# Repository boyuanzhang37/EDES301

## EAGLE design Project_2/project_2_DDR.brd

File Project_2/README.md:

Project 2
Contains the schematic, board, and the library of the DDR game board, folders contain further manufacturing information

The project: 

The entire design is a revision of project 1 rearranged into a more compact format on a PCB
  Contains 7 Segment display, 2 buzzers, 8 leds with 4 red and 4 blue, and a joystick
All components are placed on the top mianly because the input and the output of the game should be on the same side (dispaly, leds, joystick) and there were space for the buzzers and the pocketbeagel to fit without issues.

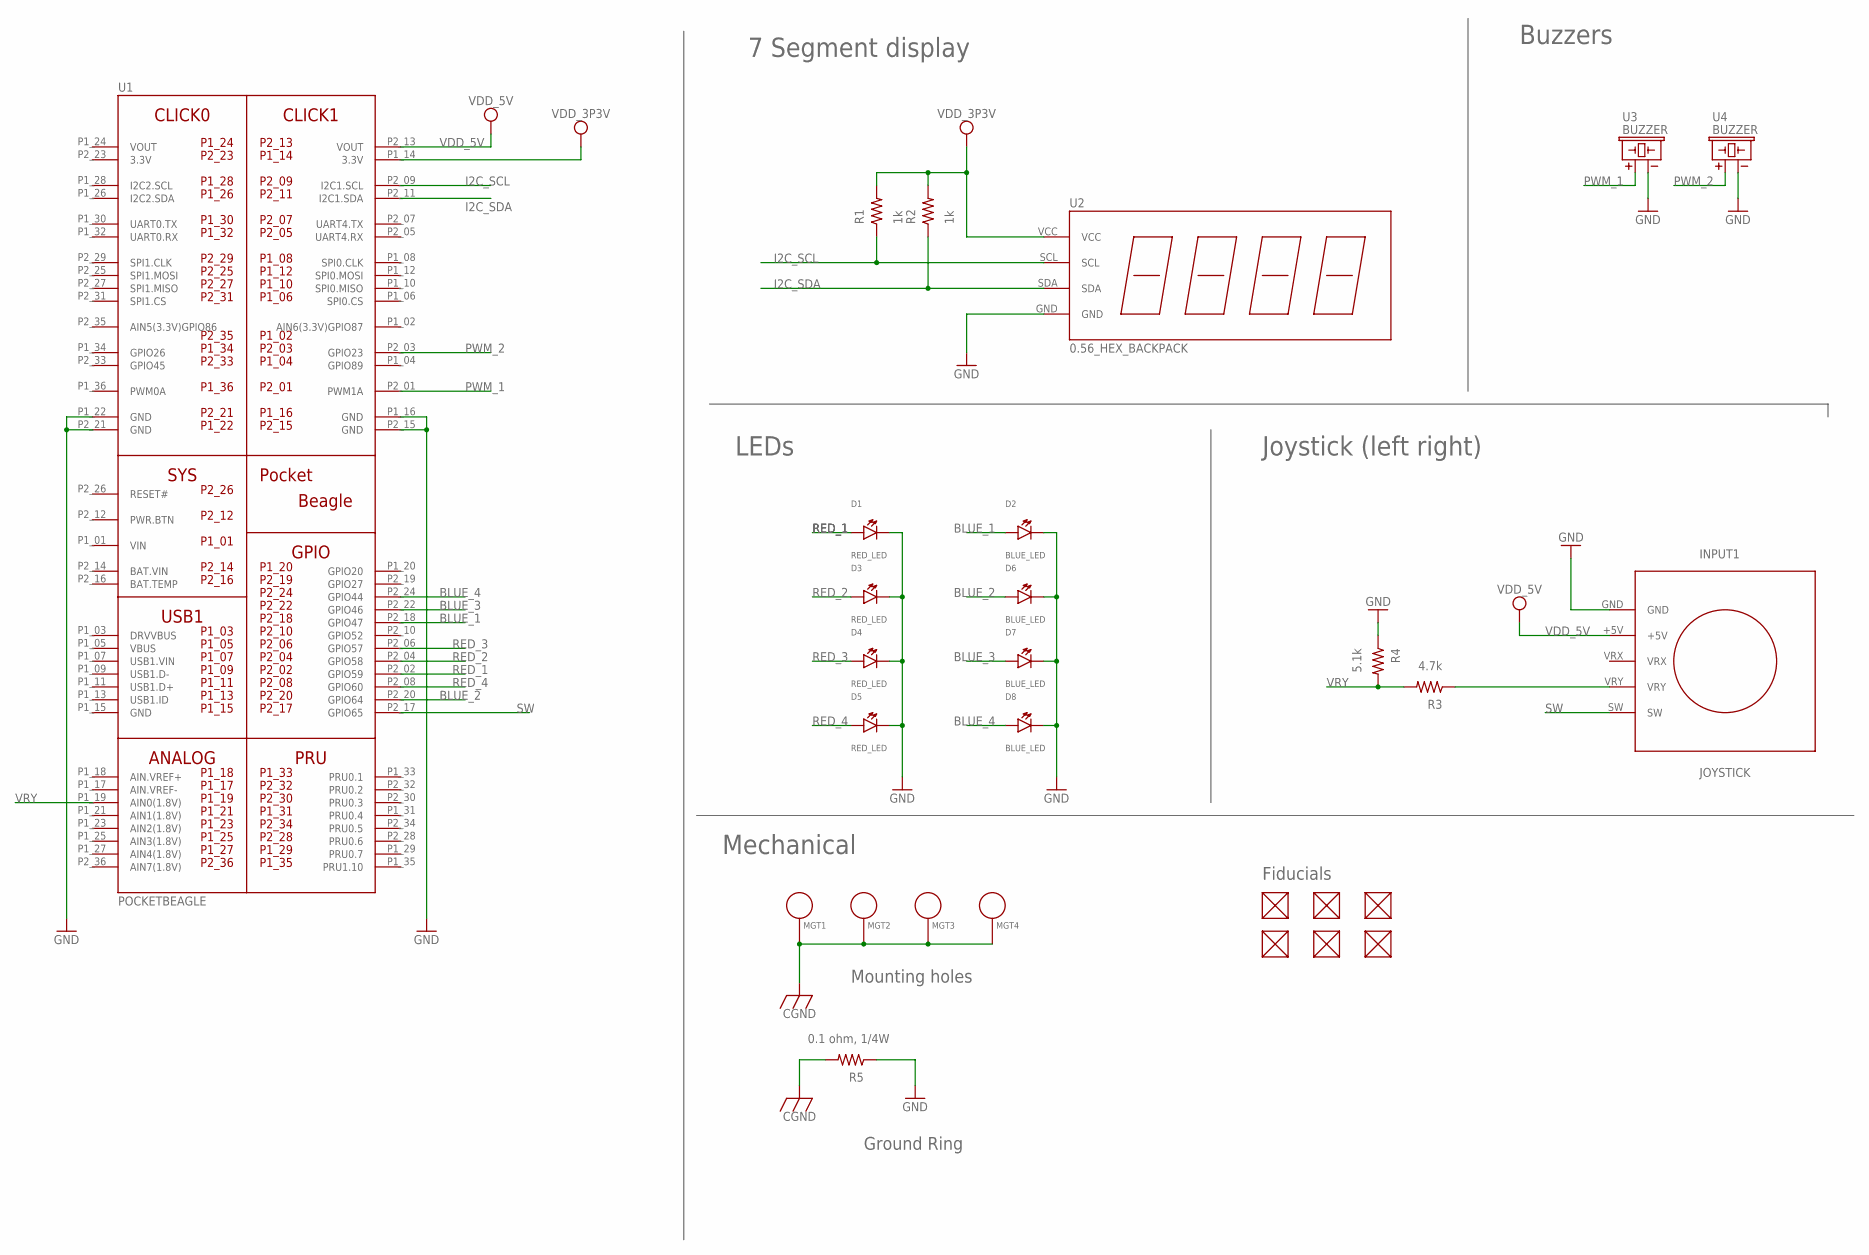
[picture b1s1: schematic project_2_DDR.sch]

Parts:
D1, D3, D4, D5: RED_LED; EIA-STD
D2, D6, D7, D8: BLUE_LED; EIA-STD
FUD1, FUD2, FUD3, FUD4, FUD5, FUD6: FIDUCIAL; FIDUCIAL_40MIL
INPUT1: JOYSTICK
MGT1, MGT2, MGT3, MGT4: MOUNTING_HOLE
R1, R2: 1k; R0603
R3: 4.7k; R0603
R4: 5.1k; R0603
R5: 0.1 ohm, 1/4W; R0603
U1: POCKETBEAGLE
U2: 0.56_HEX_BACKPACK
U3, U4: BUZZER; BUZZER_6.5MM

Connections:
3.3V: U1.P2_23 (3.3V)
BAT.VIN: U1.P2_14 (BAT.VIN)
BLUE_1: D2.ANODE, U1.P2_18 (GPIO47)
BLUE_2: D6.ANODE, U1.P2_20 (GPIO64)
BLUE_3: D7.ANODE, U1.P2_22 (GPIO46)
BLUE_4: D8.ANODE, U1.P2_24 (GPIO44)
CGND: MGT1.P$1, MGT2.P$1, MGT3.P$1, MGT4.P$1, R5.2
GND: D1.CATHODE, D2.CATHODE, D3.CATHODE, D4.CATHODE, D5.CATHODE, D6.CATHODE, D7.CATHODE, D8.CATHODE, INPUT1.GND, R4.1, R5.1, U1.P1_16 (GND), U1.P1_22 (GND), U1.P2_15 (GND), U1.P2_21 (GND), U2.GND, U3.-, U4.-
I2C_SCL: R1.1, U1.P2_09 (I2C1.SCL), U2.SCL
I2C_SDA: R2.1, U1.P2_11 (I2C1.SDA), U2.SDA
unnamed: INPUT1.VRY, R3.1
PWM_1: U1.P2_01 (PWM1A), U3.+
PWM_2: U1.P2_03 (GPIO23), U4.+
RED_1: D1.ANODE, U1.P2_02 (GPIO59)
RED_2: D3.ANODE, U1.P2_04 (GPIO58)
RED_3: D4.ANODE, U1.P2_06 (GPIO57)
RED_4: D5.ANODE, U1.P2_08 (GPIO60)
SW: INPUT1.SW, U1.P2_17 (GPIO65)
VDD_3P3V: R1.2, R2.2, U1.P1_14 (3.3V), U2.VCC
VDD_5V: INPUT1.+5V, U1.P2_13 (VOUT)
VIN: U1.P1_01 (VIN)
VOUT: U1.P1_24 (VOUT)
VRY: R3.2, R4.2, U1.P1_19 (AIN0(1.8V))

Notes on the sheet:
LEDs
Joystick (left right)
7 Segment display
Buzzers
Mechanical
Mounting holes
Fiducials
Ground Ring

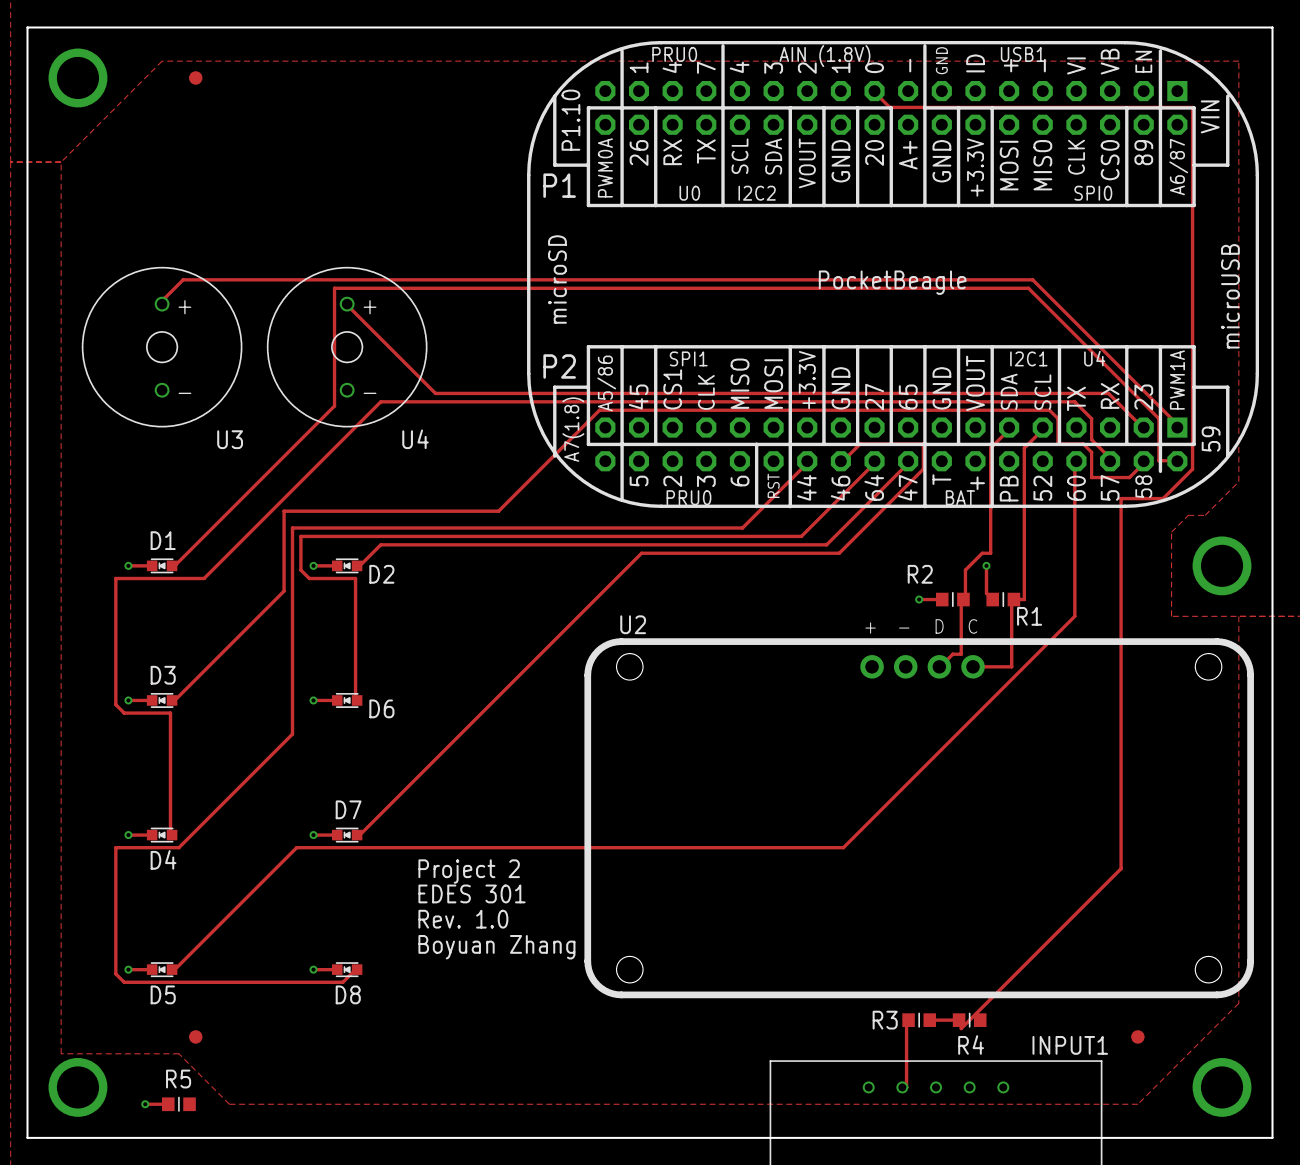
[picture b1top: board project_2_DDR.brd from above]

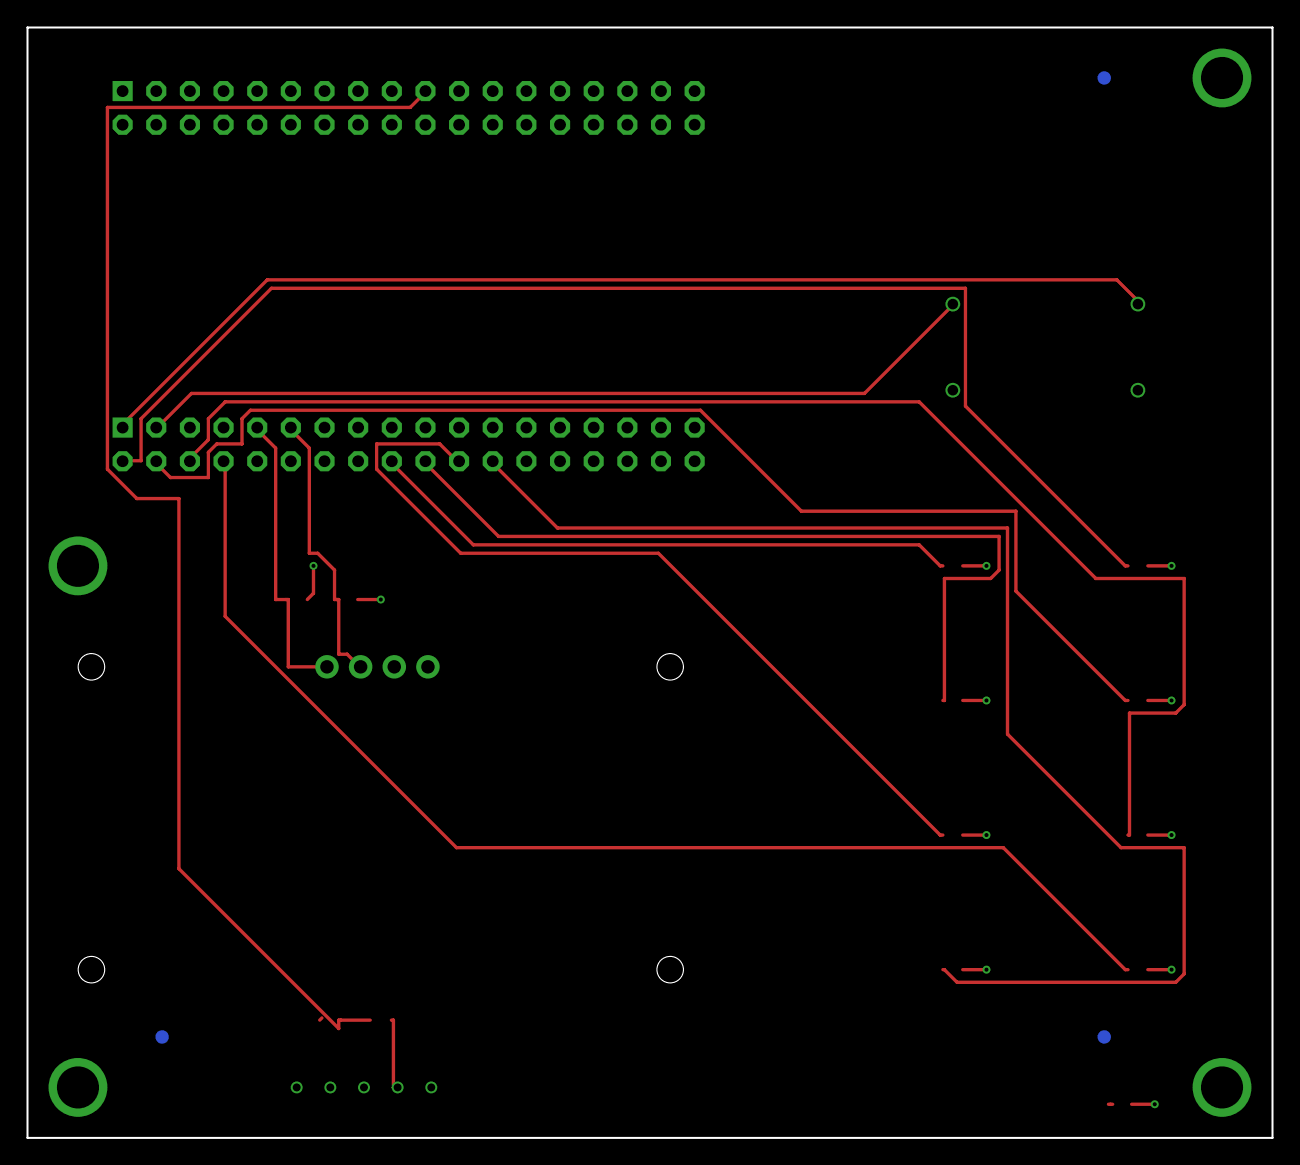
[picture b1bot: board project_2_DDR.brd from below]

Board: 4 copper layers, 94.0 x 83.8 mm, 28 parts (3 on the bottom side), 19 nets.

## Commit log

2025-09-29 add assignment_03 directory
2025-10-06 Create docs folder
2025-10-07 assignment 4
2025-12-02 Project 1
2025-12-02 J is the final code
2025-12-02 joystick testing updated
2025-12-02 Update README.txt
    updated the hackster.io link
2025-12-17 Add files via upload
    screenshots of the board and the quotes for prices for 1, 10, 100, and 1000 piece.
